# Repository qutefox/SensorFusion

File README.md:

# Board:
Top | Bottom
--- | ---
 | 

# TODOs:
- calibrate
- host interrupt pin function
- wake pin function
- remove all debug serial print lines and uninit debug serial port
- somehow make automated tests? or at least manual tests with some references
- add some documenatation: register map, usage info

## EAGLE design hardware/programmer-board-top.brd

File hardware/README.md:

# Sensor fusion board Eagle CAD files

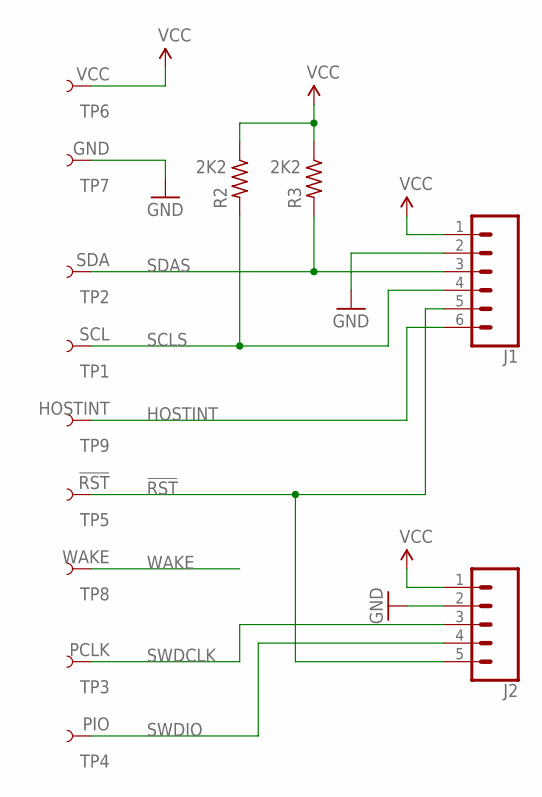
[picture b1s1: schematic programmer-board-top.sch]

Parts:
J1: CONN_06NO_SILK_FEMALE_PTH; 1X06_NO_SILK
J2: CONN_05NO_SILK; 1X05_NO_SILK
R2, R3: 2K2; R0402_B
TP1: SCL; PAD.03X.06
TP2: SDA; PAD.03X.06
TP3: PCLK; PAD.03X.06
TP4: PIO; PAD.03X.06
TP5: !RST; PAD.03X.06
TP6: VCC; PAD.03X.06
TP7: GND; PAD.03X.06
TP8: WAKE; PAD.03X.06
TP9: HOSTINT; PAD.03X.06

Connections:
!RST: J1.5, J2.5, TP5.1
GND: J1.2, J2.2, TP7.1
HOSTINT: J1.6, TP9.1
SCLS: J1.4, R2.2, TP1.1
SDAS: J1.3, R3.2, TP2.1
SWDCLK: J2.3, TP3.1
SWDIO: J2.4, TP4.1
VCC: J1.1, J2.1, R2.1, R3.1, TP6.1
WAKE: TP8.1

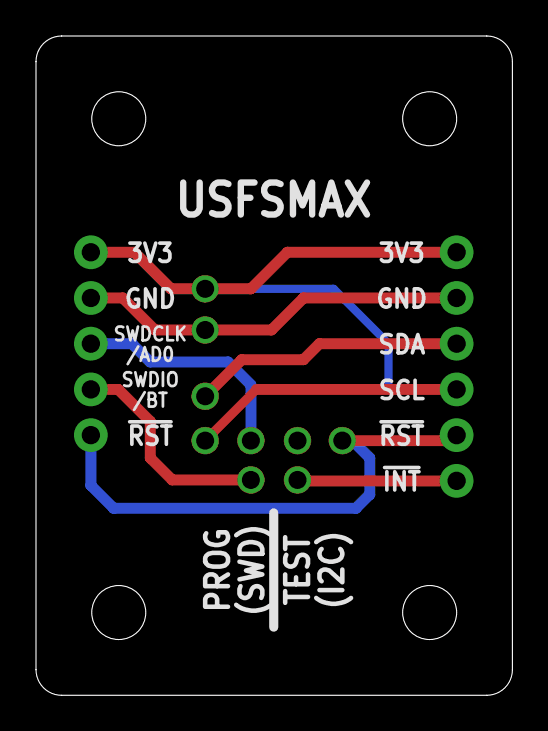
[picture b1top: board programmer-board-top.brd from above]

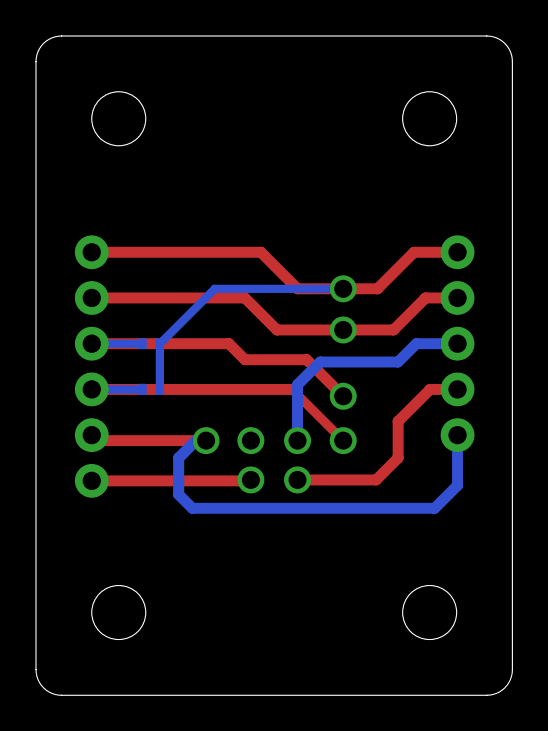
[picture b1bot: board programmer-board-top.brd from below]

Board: 2 copper layers, 26.5 x 36.6 mm, 13 parts (2 on the bottom side), 8 nets.

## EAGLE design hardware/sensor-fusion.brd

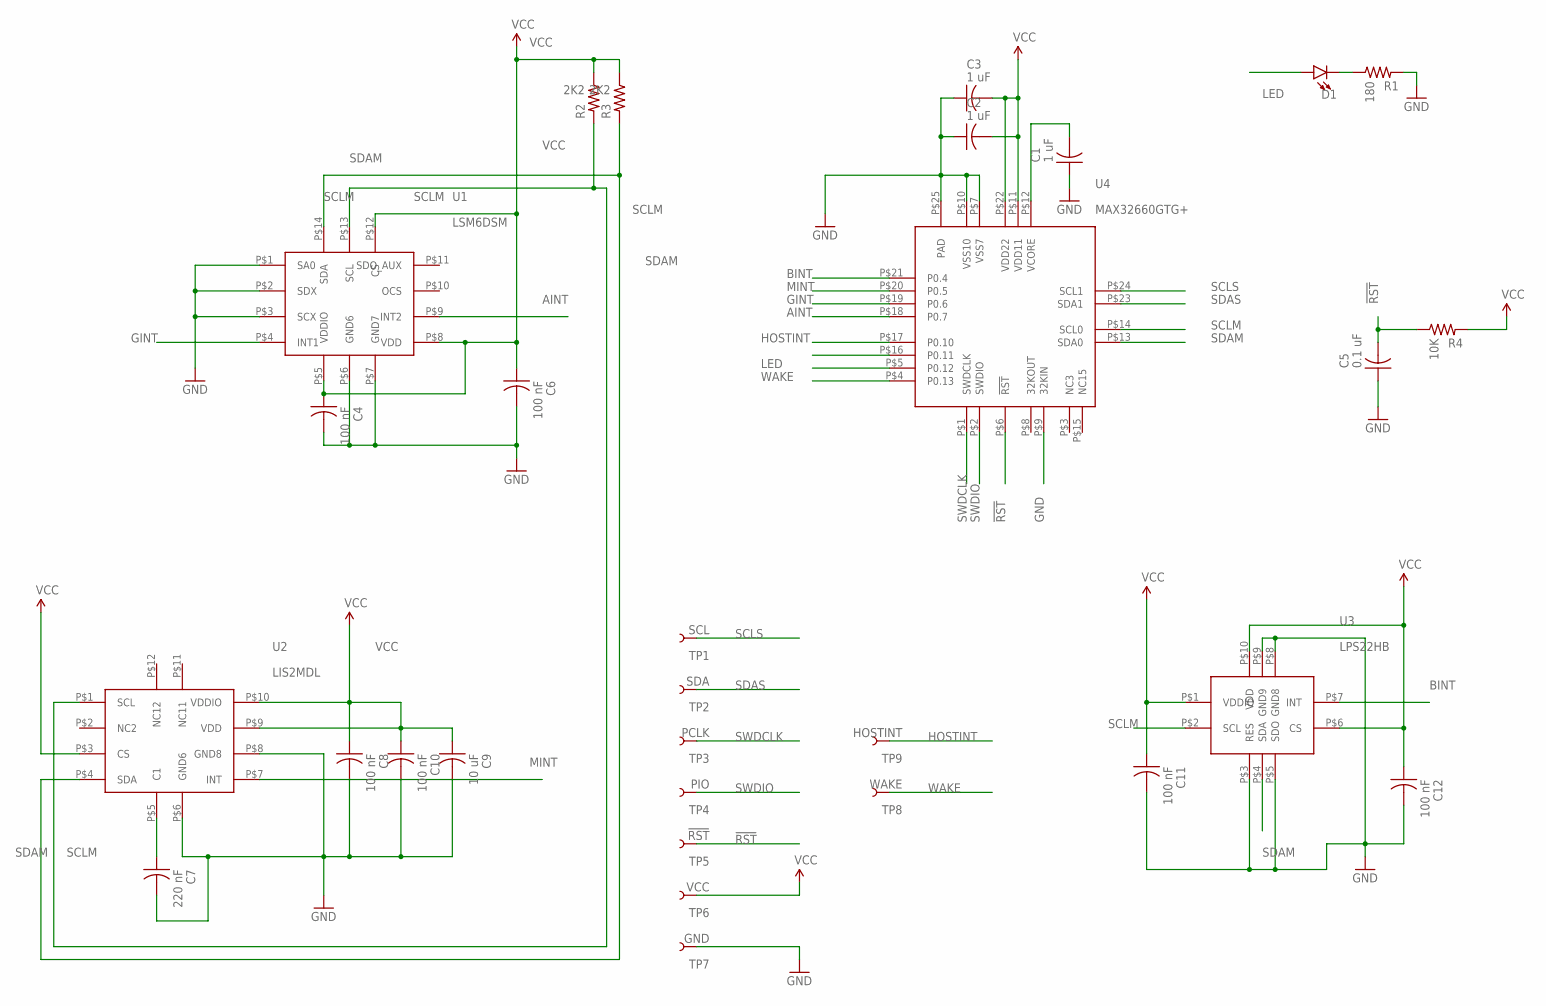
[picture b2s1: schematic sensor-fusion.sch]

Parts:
C1, C2, C3: 1 uF; C0402_B
C4, C6, C8, C10, C11, C12: 100 nF; C0402_B
C5: 0.1 uF; C0402_B
C7: 220 nF; C0402_B
C9: 10 uF; C0402_B
D1: LED0603; LED-0603
R1: 180; R0402_B
R2, R3: 2K2; R0402_B
R4: 10K; R0402_B
TP1: SCL; PAD.03X.06
TP2: SDA; PAD.03X.06
TP3: PCLK; PAD.03X.06
TP4: PIO; PAD.03X.06
TP5: !RST; PAD.03X.06
TP6: VCC; PAD.03X.06
TP7: GND; PAD.03X.06
TP8: WAKE; PAD.03X.06
TP9: HOSTINT; PAD.03X.06
U1: LSM6DSM
U2: LIS2MDL
U3: LPS22HB
U4: MAX32660GTG+

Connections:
!RST: C5.2, R4.1, TP5.1, U4.P$6 (!RST)
AINT: U1.P$9 (INT2), U4.P$18 (P0.7)
BINT: U3.P$7 (INT), U4.P$21 (P0.4)
GINT: U1.P$4 (INT1), U4.P$19 (P0.6)
GND: C1.1, C2.1, C3.1, C4.2, C5.1, C6.2, C7.2, C8.2, C9.2, C10.2, C11.2, C12.2, R1.2, TP7.1, U1.P$1 (SA0), U1.P$2 (SDX), U1.P$3 (SCX), U1.P$6 (GND6), U1.P$7 (GND7), U2.P$6 (GND6), U2.P$8 (GND8), U3.P$3 (RES), U3.P$5 (SDO), U3.P$8 (GND8), U3.P$9 (GND9), U4.P$7 (VSS7), U4.P$9 (32KIN), U4.P$10 (VSS10), U4.P$25 (PAD)
HOSTINT: TP9.1, U4.P$17 (P0.10)
LED: D1.A, U4.P$5 (P0.12)
MINT: U2.P$7 (INT), U4.P$20 (P0.5)
unnamed: C7.1, U2.P$5 (C1)
unnamed: C1.2, U4.P$12 (VCORE)
unnamed: D1.C, R1.1
OCS: U1.P$10 (OCS)
SCLM: R2.2, U1.P$13 (SCL), U2.P$1 (SCL), U3.P$2 (SCL), U4.P$14 (SCL0)
SCLS: TP1.1, U4.P$24 (SCL1)
SDAM: R3.2, U1.P$14 (SDA), U2.P$4 (SDA), U3.P$4 (SDA), U4.P$13 (SDA0)
SDAS: TP2.1, U4.P$23 (SDA1)
SDO_AUX: U1.P$11 (SDO_AUX)
SWDCLK: TP3.1, U4.P$1 (SWDCLK)
SWDIO: TP4.1, U4.P$2 (SWDIO)
VCC: C2.2, C3.2, C4.1, C6.1, C8.1, C9.1, C10.1, C11.1, C12.1, R2.1, R3.1, R4.2, TP6.1, U1.P$5 (VDDIO), U1.P$8 (VDD), U1.P$12 (CS), U2.P$3 (CS), U2.P$9 (VDD), U2.P$10 (VDDIO), U3.P$1 (VDDIO), U3.P$6 (CS), U3.P$10 (VDD), U4.P$11 (VDD11), U4.P$22 (VDD22)
WAKE: TP8.1, U4.P$4 (P0.13)

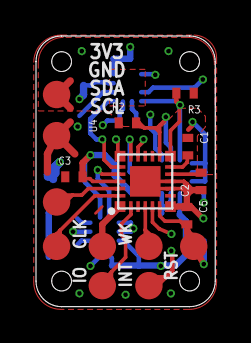
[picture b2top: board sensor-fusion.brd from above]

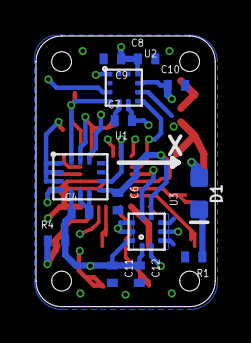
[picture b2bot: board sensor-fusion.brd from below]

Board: 4 copper layers, 10.0 x 15.0 mm, 30 parts (14 on the bottom side), 19 nets.

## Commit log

2023-10-27 Added upload instructions.
2023-10-27 Added sensor driver submodules
2023-10-27 Added IDE setup guide
2023-10-27 IDE changes.
2023-10-27 Added eagle CAD files.
2023-10-27 LPS22HB barometric sensor first steps.
2023-10-27 Removing git submodules
2023-10-27 Removed submodule
2023-10-27 Adding in "dirty" sensor drivers.
2023-10-28 Split pinio into input_pin and ouput pin. Input pin received "attach_interrupt_callback" method.
2023-10-28 Added back (forked and fixed) submodule repos.
2023-10-28 Added basic register map for i2c slave memory area.
2023-10-29 Added i2c slave component. Rewrote existing components to follow singleton pattern.
2023-10-29 First round of i2c slave fixes. Register writing seems to work. Reading causes error where we immediately go to transaction close event. Needs more troubleshooting.
2023-10-29 Fixed i2c slave mode.
2023-10-30 Improved i2c slave: main thread no longer has to continuously poll the state and start the next async task. The interrupt handler will automatically do this. Added register map reader writer class to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
2023-10-30 Added test data processor where "business logic" is going to be implemented. (Separated register map responsibilities into different classes.)
2023-11-02 Rewritten register handling and register map init code because previous version was hard to expand/change. Any (new) register change (insert ot the middle of the map) required to move the address of 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
2023-11-03 Added sleep/wakeup for main thread.
2023-11-03 Added sensor interface. Added some initial lsm6dsm gyro/accel sensor code.
2023-11-04 Inertial sensor module is now running in FIFO mode. Added power mode selection to the sensor interface.
2023-11-05 Trying to add submodule.
2023-11-05 Trying to add submodule
2023-11-05 Added fusion submodule from https://github.com/xioTechnologies/Fusion.
2023-11-05 Added magnetic sensor init code.
2023-11-05 Data processor interface improvement to receive all sensor data.
2023-11-06 This is the time when I realise sensors should not use FIFO :) This is also the time when I realise the fusion algorythm requires delta time and the RTC functionality will only work on the MCU if the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
2023-11-11 [IMPROVEMENT] Rewrite the sensor codes to not use fifo. Added interface classes to most of the components. Current code is to test the lsm6dsm timestamp feature.
2023-11-17 [FIX] Finally understood that reading sensor data inside interrupts is a bad idea and causes a system "crash" becuase multiple i2c communications overlap. I2c master debug variable was always overwri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
2023-11-25 [IMPROVEMENT] Added flash read, write to store calibration configuration in the future. Fixed initialise codes. Simplified interfaces.
2023-11-25 [FIX] Sensor fusion start/stop bit was a bad design, because after handling the start bit, we clear out the flag. Writing zero to that flag did not trigger a change event afterwards. Separated the 1 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
2023-12-01 [IMPROVEMENT] Added calibration data. Reworked register map. Fixed i2c slave bus off recovery. Separated data processor into controller and fusion data modules.
2023-12-08 [FIX] Fixed sensor units and made test code for Circuitpython host MCU. Also made a python tool for windows to read the circuitpython host via serial port and visualise the quaterion data with a cube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
2023-12-09 [IMPROVEMENT] Updated tester/visualizer python script to render text (with opengl) showing some basic data.
2023-12-10 [IMPROVEMENT] Added option to disable/enable euler and earth output.
2023-12-11 [FIX] Setting power mode in circuitpython host library was wrong. Caused to power down sensors. Also there is something wrong with the high performance mode in the inertial sensor. Will have too look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
2023-12-18 [IMPROVEMENT] Adding demo details.
2023-12-18 Readme change.
2023-12-18 Redme change.
2023-12-18 Flipped board bottom side image to match the top side image of the board.
2023-12-21 [FIX] Missed i2c pullup resistors from wiring diagram. Typo fixes.

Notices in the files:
parts and their libraries:
test-pad: Licensing: Creative Commons ShareAlike 4.0 International - https://creativecommons.org/licenses/by-sa/4.0
SparkFun-Aesthetics: Licensing: CC v3.0 Share-Alike You are welcome to use this library for commercial purposes.
